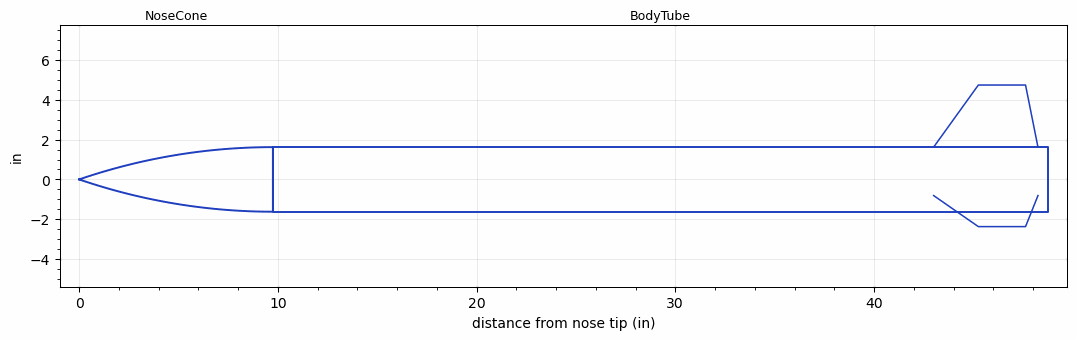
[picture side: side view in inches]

<RASAeroDocument>
 <FileVersion>2</FileVersion>
 <RocketDesign>
  <NoseCone>
   <Length>9.75</Length>
   <Diameter>3.25</Diameter>
   <Shape>Tangent Ogive</Shape>
   <Location>0</Location>
  </NoseCone>
  <BodyTube>
   <Length>39</Length>
   <Diameter>3.25</Diameter>
   <Location>9.75</Location>
   <Fin>
    <Count>3</Count>
    <Chord>5.25</Chord>
    <Span>3.125</Span>
    <SweepDistance>2.25</SweepDistance>
    <TipChord>2.375</TipChord>
    <Thickness>0.125</Thickness>
    <Location>5.75</Location>
    <AirfoilSection>Square</AirfoilSection>
   </Fin>
  </BodyTube>
  <Surface>Smooth (Zero Roughness)</Surface>
  <ModifiedBarrowman>False</ModifiedBarrowman>
  <Turbulence>True</Turbulence>
  <UseBooster1>False</UseBooster1>
  <UseBooster2>False</UseBooster2>
  <Comments>Final independent static CP evaluation, three-fin-moderate</Comments>
 </RocketDesign>
 <LaunchSite>
  <Altitude>0</Altitude>
  <Pressure>29.9214</Pressure>
  <RodAngle>0</RodAngle>
  <RodLength>6.5617</RodLength>
  <Temperature>59</Temperature>
  <WindSpeed>0</WindSpeed>
 </LaunchSite>
 <Recovery>
  <Altitude1>0</Altitude1>
  <Altitude2>0</Altitude2>
  <DeviceType1>None</DeviceType1>
  <DeviceType2>None</DeviceType2>
  <Event1>False</Event1>
  <Event2>False</Event2>
  <Size1>0</Size1>
  <Size2>0</Size2>
  <EventType1>None</EventType1>
  <EventType2>None</EventType2>
  <CD1>0</CD1>
  <CD2>0</CD2>
 </Recovery>
</RASAeroDocument>
